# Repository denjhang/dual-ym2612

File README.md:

# dual-ym2612
Dual ym2612 music synthesizer
## Originate 
from https://gendev.spritesmind.net/forum/viewtopic.php?f=24&t=1470&sid=01c3a0eb5cf9f0443d67a1da09db6ff7

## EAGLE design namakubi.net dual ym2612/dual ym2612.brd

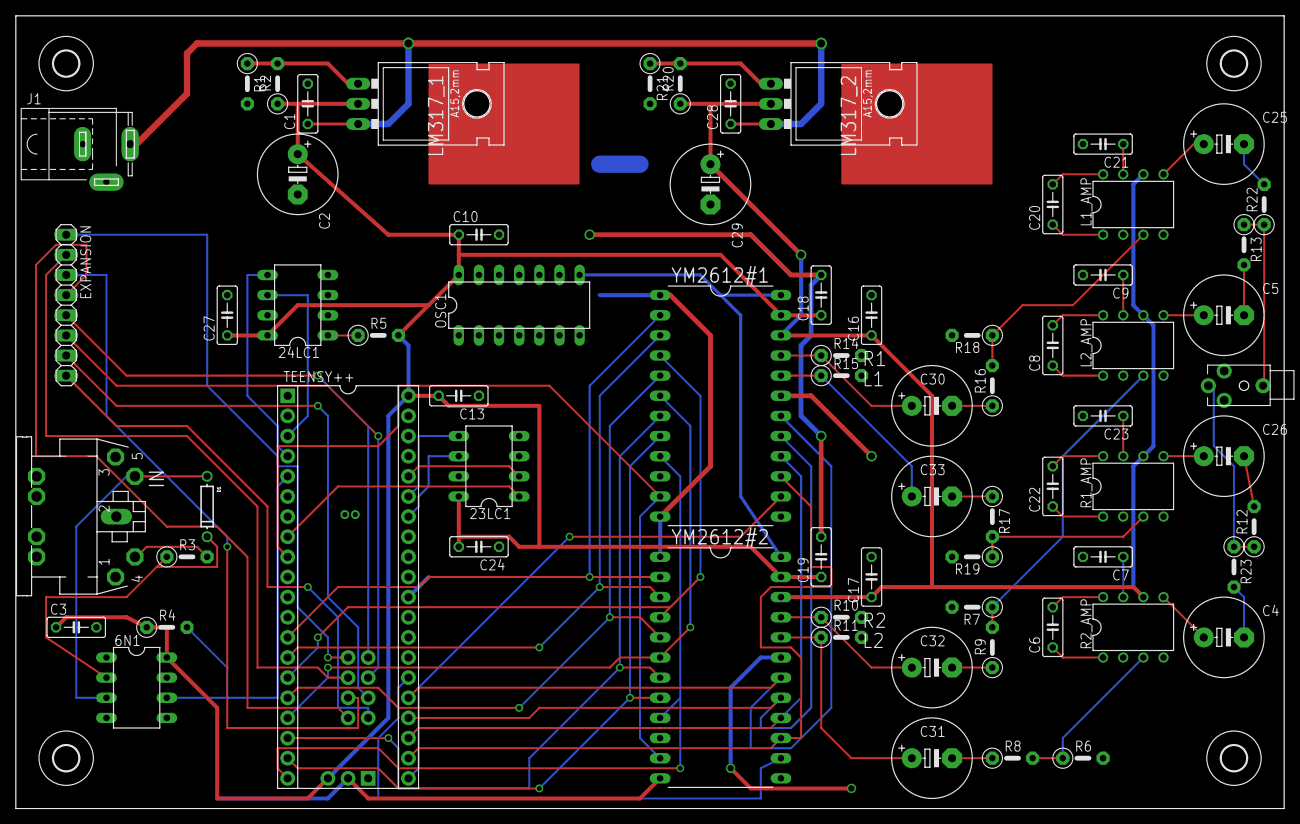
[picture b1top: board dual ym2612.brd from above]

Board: 2 copper layers, 160.0 x 100.0 mm, 74 parts (0 on the bottom side), 75 nets.

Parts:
6N1, 23LC1, 24LC1: DIL08
AUDIO: STEREOJACK2.5MM_STEREOJACK2.5MM
C1, C3, C7, C9, C10, C16, C17, C18, C19, C21, C23, C24, C27, C28: 0.1bp; C050-025X075
C2, C29: 1bp; E5-10,5
C4, C5, C25, C26, C30, C31, C32, C33: E5-10,5
C6, C8, C20, C22: 10uf; C050-025X075
C13: 1bp; C050-025X075
D1: DO-1N4148
EXPANSION: 1X08
H1, H2, H3, H4: MOUNT-HOLE3.2; 3,2
IN: MIDIJACK; CP-2350
J1: SPC4078
L1_AMP, L2_AMP: LM386N-1; DIL08
LM317_1, LM317_2: 317TL
OSC1: 7.68mhz; DIL14
R1, R4, R21: 1k; 0207/5V
R1_AMP, R2_AMP: LM386N-1; DIL08
R2, R20: 330; 0207/5V
R3: 220; 0207/5V
R5, R12, R13, R22, R23: 10k; 0207/5V
R6, R7, R10, R11, R14, R15, R18, R19: 12k; 0207/5V
R8, R9, R16, R17: 220k; 0207/5V
TEENSY++: ARDUINO-TEENSY++; TEENSY++
YM2612#1, YM2612#2: YM2612; DIL24-6

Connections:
+5V: 6N1.8, 23LC1.8, 24LC1.8, C2.+, C3.1, C10.1, C13.2, C18.1, C19.1, C24.2, C27.1, LM317_1.2, OSC1.14, R2.1, R4.1, R5.2, TEENSY++.5V, TEENSY++.+5V, YM2612#1.23, YM2612#2.23
DATA0: TEENSY++.C0, YM2612#1.2, YM2612#2.2
DATA1: TEENSY++.C1, YM2612#1.3, YM2612#2.3
DATA2: TEENSY++.C2, YM2612#1.4, YM2612#2.4
DATA3: TEENSY++.C3, YM2612#1.5, YM2612#2.5
DATA4: TEENSY++.C4, YM2612#1.6, YM2612#2.6
DATA5: TEENSY++.C5, YM2612#1.7, YM2612#2.7
DATA6: TEENSY++.C6, YM2612#1.8, YM2612#2.8
DATA7: TEENSY++.C7, YM2612#1.9, YM2612#2.9
GND: 6N1.5, 23LC1.4, 24LC1.2, 24LC1.3, 24LC1.4, 24LC1.7, AUDIO.RING1, C1.2, C2.-, C3.2, C7.2, C9.2, C10.2, C13.1, C16.2, C17.2, C18.2, C19.2, C21.2, C23.2, C24.1, C27.2, C28.2, C29.-, J1.1, J1.2, L1_AMP.2, L1_AMP.4, L2_AMP.2, L2_AMP.4, OSC1.7, R1.2, R1_AMP.2, R1_AMP.4, R2_AMP.2, R2_AMP.4, R6.2, R7.2, R10.2, R11.2, R14.2, R15.2, R18.2, R19.2, R21.2, TEENSY++.GND, TEENSY++.GND2, TEENSY++.GRND1, YM2612#1.1, YM2612#1.12, YM2612#1.19, YM2612#2.1, YM2612#2.12, YM2612#2.19
unnamed: TEENSY++.D6, YM2612#1.11, YM2612#2.11
unnamed: TEENSY++.F7, YM2612#1.14
unnamed: TEENSY++.F2, YM2612#2.14
unnamed: TEENSY++.F3, YM2612#1.18, YM2612#2.18
unnamed: TEENSY++.F4, YM2612#1.17, YM2612#2.17
unnamed: TEENSY++.F5, YM2612#1.16, YM2612#2.16
unnamed: TEENSY++.F6, YM2612#1.15, YM2612#2.15
unnamed: OSC1.8, YM2612#1.24, YM2612#2.24
unnamed: IN.4, R3.2
unnamed: EXPANSION.1, TEENSY++.A0
unnamed: 6N1.3, D1.A, IN.5
unnamed: 6N1.2, D1.C, R3.1
unnamed: C33.+, R15.1, YM2612#1.20
unnamed: C30.+, R14.1, YM2612#1.21
unnamed: 24LC1.1, R5.1
unnamed: C31.-, R8.1
unnamed: R2_AMP.3, R6.1, R8.2
unnamed: 24LC1.5, TEENSY++.D1
unnamed: 24LC1.6, TEENSY++.D0
unnamed: 23LC1.5, TEENSY++.B2
unnamed: 23LC1.6, TEENSY++.B1
unnamed: 23LC1.1, TEENSY++.D5
unnamed: 23LC1.2, TEENSY++.B3
unnamed: 6N1.6, R4.2, TEENSY++.D2
unnamed: EXPANSION.2, TEENSY++.A1
unnamed: EXPANSION.3, TEENSY++.A2
unnamed: EXPANSION.4, TEENSY++.A3
unnamed: EXPANSION.5, TEENSY++.A4
unnamed: EXPANSION.6, TEENSY++.A5
unnamed: EXPANSION.7, TEENSY++.A6
unnamed: EXPANSION.8, TEENSY++.A7
unnamed: C6.1, R2_AMP.1
unnamed: C32.+, R10.1, YM2612#2.21
unnamed: C31.+, R11.1, YM2612#2.20
unnamed: C6.2, R2_AMP.8
unnamed: C7.1, R2_AMP.7
unnamed: C30.-, R16.1
unnamed: L1_AMP.3, R16.2, R18.1
unnamed: C20.1, L1_AMP.1
unnamed: C20.2, L1_AMP.8
unnamed: C21.1, L1_AMP.7
unnamed: C33.-, R17.1
unnamed: L2_AMP.3, R7.1, R9.2
unnamed: C8.1, L2_AMP.1
unnamed: C8.2, L2_AMP.8
unnamed: C9.1, L2_AMP.7
unnamed: C32.-, R9.1
unnamed: R1_AMP.3, R17.2, R19.1
unnamed: C22.1, R1_AMP.1
unnamed: C22.2, R1_AMP.8
unnamed: C23.1, R1_AMP.7
unnamed: C5.+, L2_AMP.5
unnamed: C4.+, R2_AMP.5
unnamed: C25.+, L1_AMP.5
unnamed: C26.+, R1_AMP.5
unnamed: C25.-, R22.2
unnamed: AUDIO.TIP, R12.1, R23.1
unnamed: C4.-, R23.2
unnamed: AUDIO.SHIELD, R13.1, R22.1
unnamed: C5.-, R13.2
unnamed: C1.1, C28.1, J1.3, LM317_1.3, LM317_2.3
unnamed: C26.-, R12.2
unnamed: LM317_1.1, R1.1, R2.2
unnamed: LM317_2.1, R20.2, R21.1
VDD: C16.1, C17.1, C29.+, L1_AMP.6, L2_AMP.6, LM317_2.2, R1_AMP.6, R2_AMP.6, R20.1, YM2612#1.22, YM2612#2.22

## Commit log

2021-04-05 initial
2021-04-05 Description

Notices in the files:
parts and their libraries:
SparkFun-Connectors: Licensing: CC v3.0 Share-Alike You are welcome to use this library for commercial purposes.
